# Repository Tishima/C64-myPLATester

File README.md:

# C64 myPLATester shield - PLA 906114-01
The myPLATester shield is a Arduino Mega shield , to test the C64 PLA 906114-01 or his clones like the GAL PAL.
It check all output vectors  via all input vectors and shows the result with a LED or serial output

Its based on the work from AC Lovell - ACs 8-Bit Zone
for more information look at his Video
https://www.youtube.com/watch?v=Yru8bx_IqN8

This repository contains all eagle files, gerber file, BOM, schematics, a little adjusted Arduino source code for my shield hardware, based on ACs code

Depending on where the parts and pcbs are purchased, the price for the complete shield is around 20€ (2023), without Arduino Mega and power supply
I built this project to find a issue with the GAL PLA from https://www.freepascal.org/~daniel/c64pla/, but the problem was only a wrong programming failure of my site.

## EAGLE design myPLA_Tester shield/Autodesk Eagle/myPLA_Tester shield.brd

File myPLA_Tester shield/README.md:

# C64 myPLATester shield - PLA 906114-01
The myPLATester shield is a Arduino Mega shield , to test the C64 PLA 906114-01 or his clones like the GAL PAL.
It check all output vectors  via all Input Vectors and shows the result with a LED or serial output

Its based on the work from AC Lovell - ACs 8-Bit Zone
for more information look at his Video
https://www.youtube.com/watch?v=Yru8bx_IqN8

This repository contains all eagle files, gerber file, BOM, schematics, a little adjusted Arduino source code for my shield hardware, based on ACs code

Depending on where the parts and pcbs are purchased, the price for the complete shield is around 20€ (2023), without Arduino Mega and power supply
I built this project for find a issue with the GAL PLA from https://www.freepascal.org/~daniel/c64pla/, but the problem was only a wrong programming failure of my site.

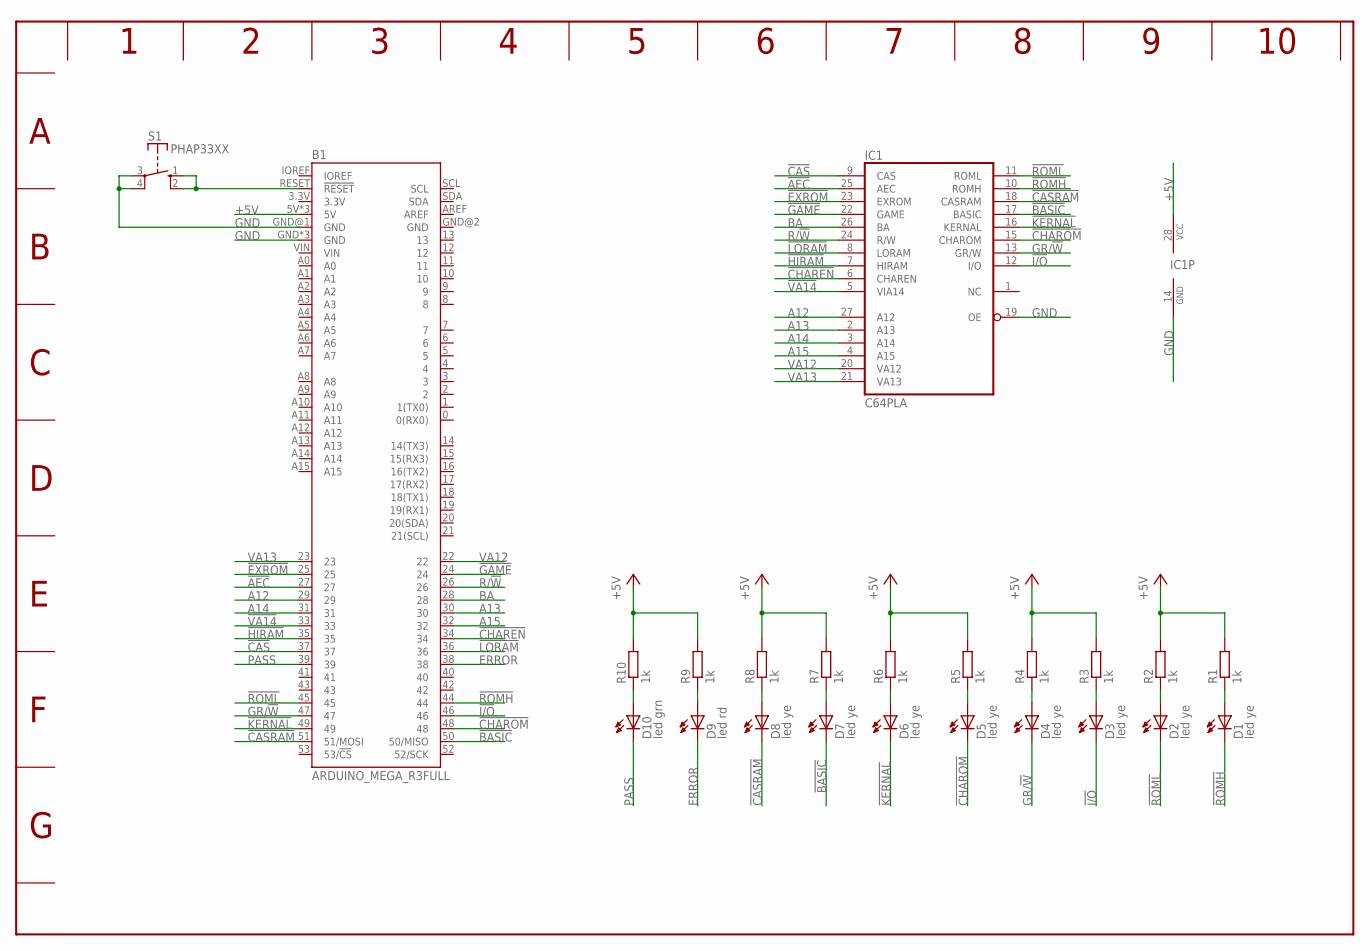
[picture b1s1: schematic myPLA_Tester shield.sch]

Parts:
B1: ARDUINO_MEGA_R3FULL; ARDUINO_MEGA_NO_SILK
D1, D2, D3, D4, D5, D6, D7, D8: led ye; LED3MM
D9: led rd; LED3MM
D10: led grn; LED3MM
IC1: C64PLA; DIL28
R1, R2, R3, R4, R5, R6, R7, R8, R9, R10: 1k; 0207/10
S1: PHAP33XX

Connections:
!AEC: B1.27, IC1.25 (AEC)
!BASIC: B1.50 (50/MISO), D7.K (C), IC1.17 (BASIC)
!CAS: B1.37, IC1.9 (CAS)
!CASRAM: B1.51 (51/MOSI), D8.K (C), IC1.18 (CASRAM)
!CHAREN: B1.34, IC1.6 (CHAREN)
!CHAROM: B1.48, D5.K (C), IC1.15 (CHAROM)
!EXROM: B1.25, IC1.23 (EXROM)
!GAME: B1.24, IC1.22 (GAME)
!HIRAM: B1.35, IC1.7 (HIRAM)
!I/O: B1.46, D3.K (C), IC1.12 (I/O)
!KERNAL: B1.49, D6.K (C), IC1.16 (KERNAL)
!LORAM: B1.36, IC1.8 (LORAM)
!ROMH: B1.44, D1.K (C), IC1.10 (ROMH)
!ROML: B1.45, D2.K (C), IC1.11 (ROML)
!VA14: B1.33, IC1.5 (VIA14)
+5V: B1.5V, B1.5V@1 (5V), B1.5V@2 (5V), IC1.28 (VCC), R1.2, R2.2, R3.2, R4.2, R5.2, R6.2, R7.2, R8.2, R9.2, R10.2
A12: B1.29, IC1.27 (A12)
A13: B1.30, IC1.2 (A13)
A14: B1.31, IC1.3 (A14)
A15: B1.32, IC1.4 (A15)
BA: B1.28, IC1.26 (BA)
ERROR: B1.38, D9.K (C)
GND: B1.GND, B1.GND@1 (GND), B1.GND@3 (GND), B1.GND@4 (GND), IC1.14 (GND), IC1.19 (OE), S1.3, S1.4
GR/!W: B1.47, D4.K (C), IC1.13 (GR/W)
unnamed: D2.A, R2.1
unnamed: D1.A, R1.1
unnamed: D10.A, R10.1
unnamed: D9.A, R9.1
unnamed: D8.A, R8.1
unnamed: D7.A, R7.1
unnamed: D6.A, R6.1
unnamed: D5.A, R5.1
unnamed: D4.A, R4.1
unnamed: D3.A, R3.1
unnamed: B1.RESET (!RESET), S1.1 (S), S1.2 (S)
PASS: B1.39, D10.K (C)
R/!W: B1.26, IC1.24 (R/W)
VA12: B1.22, IC1.20 (VA12)
VA13: B1.23, IC1.21 (VA13)

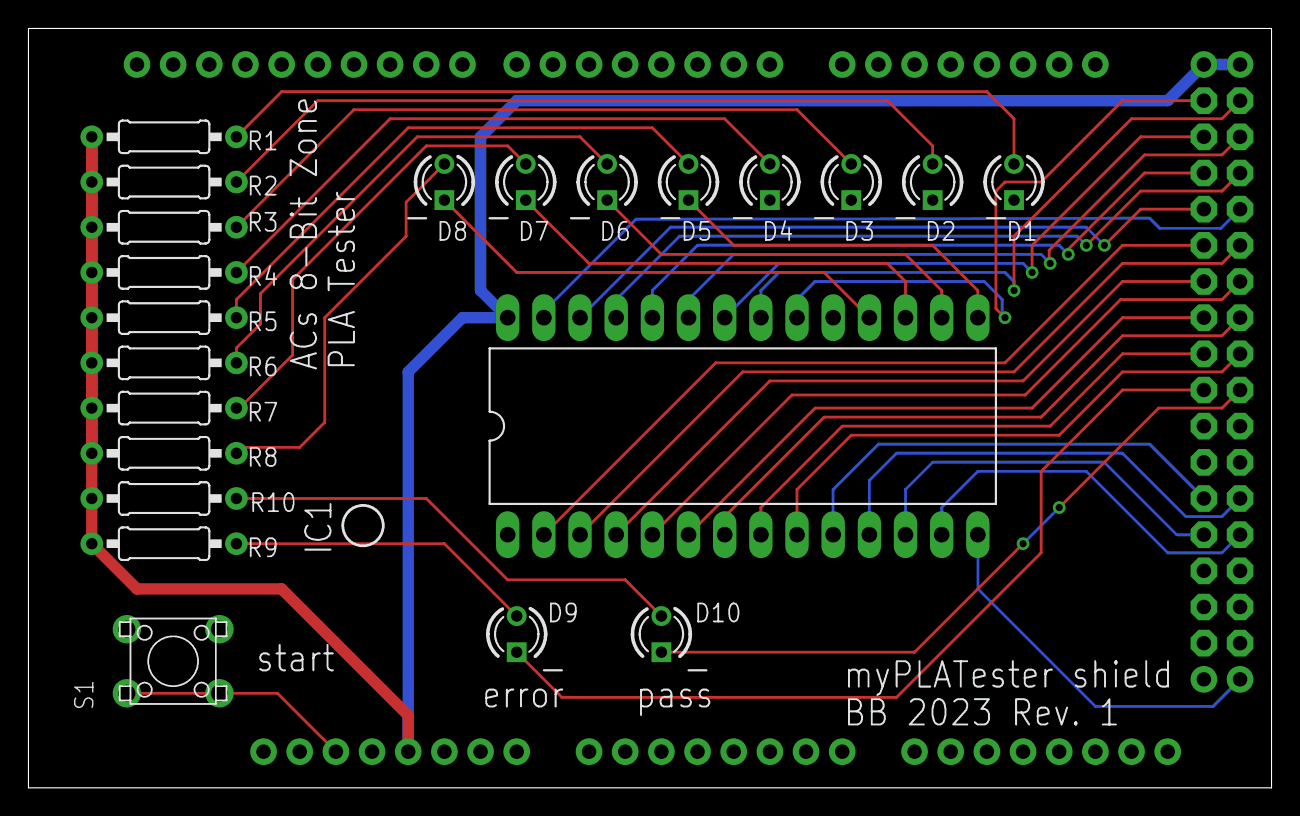
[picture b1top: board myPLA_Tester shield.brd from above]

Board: 4 copper layers, 87.3 x 53.3 mm, 23 parts (0 on the bottom side), 39 nets.

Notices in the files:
parts and their libraries:
SparkFun-Boards: Licensing: Creative Commons ShareAlike 4.0 International - https://creativecommons.org/licenses/by-sa/4.0
